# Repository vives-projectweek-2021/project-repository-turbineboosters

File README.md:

# TurbineBoosters
Welcome to our project repository!

## Choice of motor

To create our windturbine we had to make some choices. The first choice we had to make was wich motor to use as generator.
It soon became clear to us that we had to use a 3 phasse BLDC motor.
We looked around at our options and had 2 motors available, one that generates around 60V:

and another one that generates only around 6V, but has more power:

We decided to go for the motor that generates 60V because we lose 1,4V across the diodes of our 3 phase bridge rectifier and that leaves us with an efficiency of 96%, while the other motor would only offer us an efficiency of about 77%.

## Rectifier + first LoRa module

The power generated by our motor is fed to a 3 phase bridge rectifier.
On this board we measure the current and voltage via a shunt-resistor of 0,5Ω.
The LoRa module (RN2483A) receives this data and sends it peer-to-peer to another LoRa module:

## Lorawan receiver 

The data that we recieve over lorawan on the SODAQ Explorer microconroller is than formated to a byte array. Then the data is send over bluetooth and send to a raspberry pi.

First we wanted to send the data over bluetooth low energy that was on the controller. But the bleutooth HC05 chip doesn't take that much power and is easier to use. 

## Raspberry pi

The data that we receive over bluetooth is than but into an influxdb database. This data is than visualized with the use of grafana.

## Mechanical design

We mounted a bicycle wheel on the shaft of our motor, to which we attached 8 PVC-blades via 3D-printed coupling pieces.

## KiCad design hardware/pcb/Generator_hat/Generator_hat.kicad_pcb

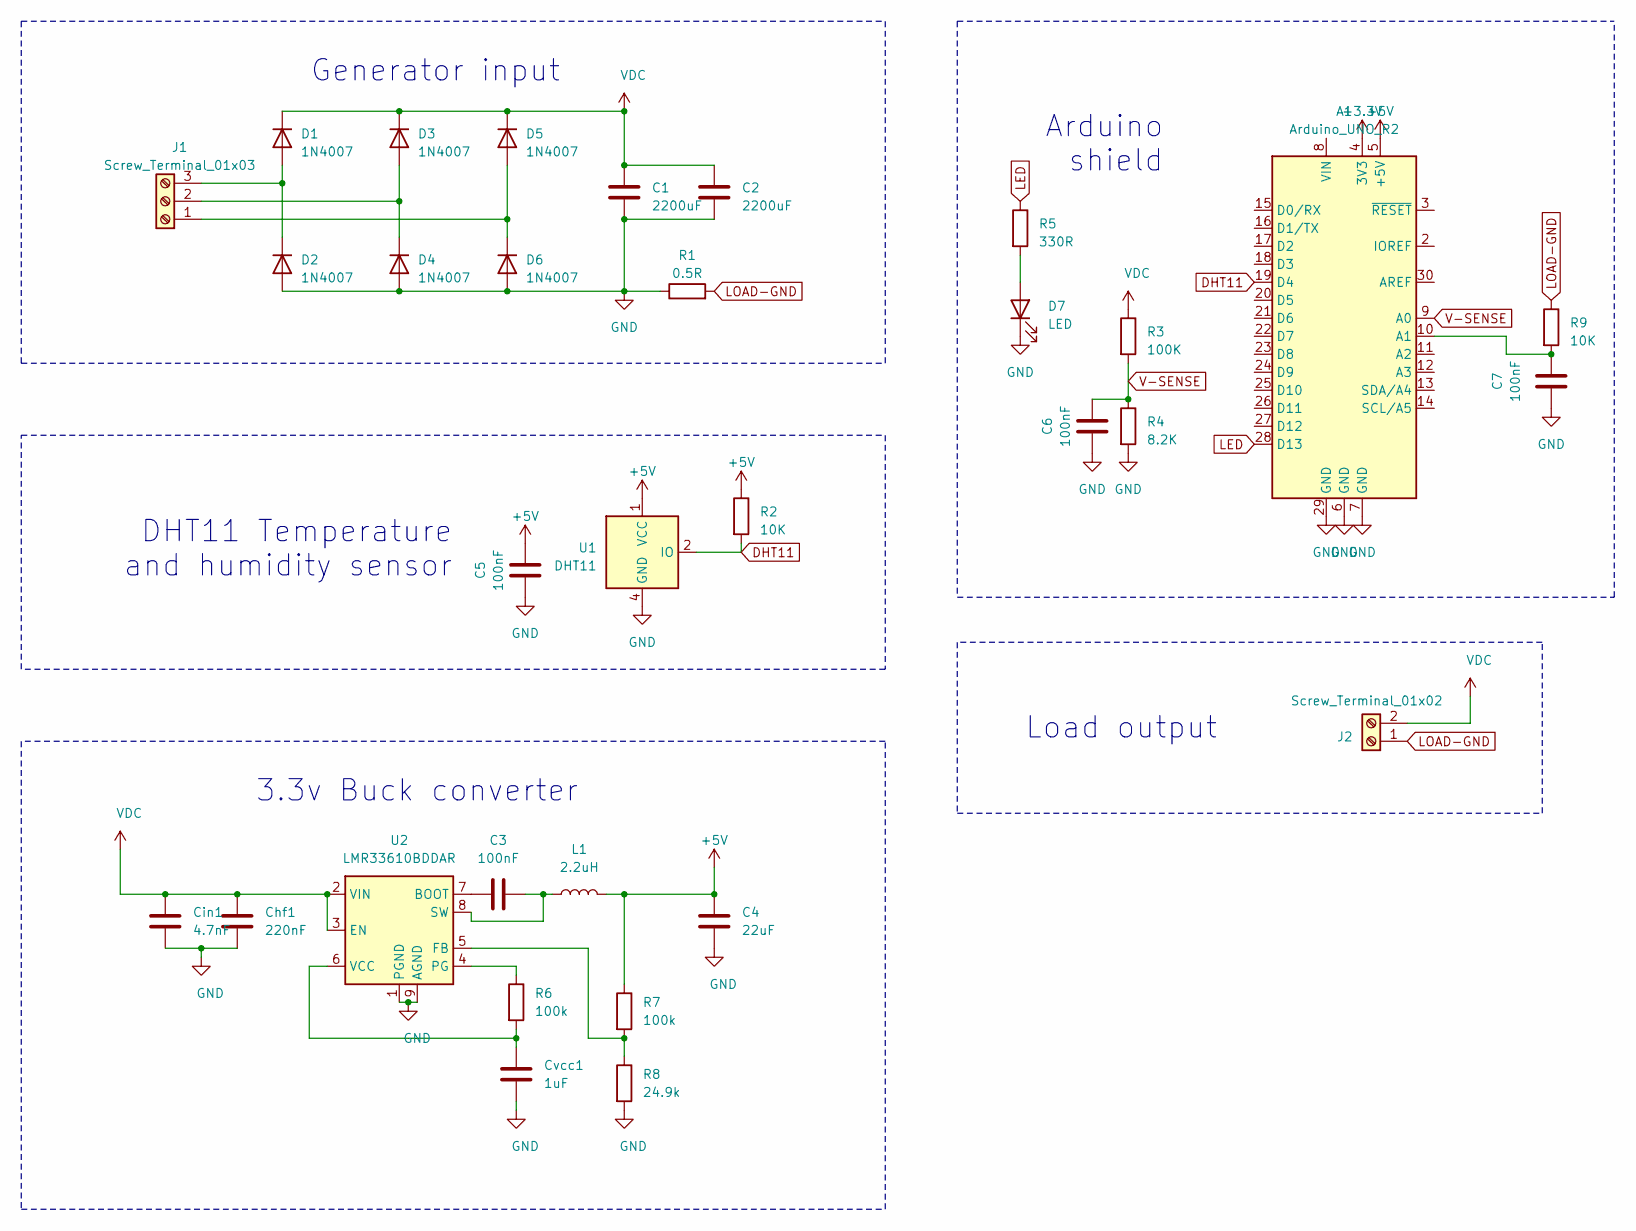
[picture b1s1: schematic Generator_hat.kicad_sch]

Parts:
A1: Arduino_UNO_R2
C1, C2: 2200uF; CP_Radial_D16.0mm_P7.50mm
C3, C5, C6, C7: 100nF; C_0805_2012Metric_Pad1.18x1.45mm_HandSolder
C4: 22uF; CP_Elec_8x6.9
Chf1: 220nF; C_0805_2012Metric_Pad1.18x1.45mm_HandSolder
Cin1: 4.7nF; C_0805_2012Metric_Pad1.18x1.45mm_HandSolder
Cvcc1: 1uF; C_0805_2012Metric_Pad1.18x1.45mm_HandSolder
D1, D2, D3, D4, D5, D6: 1N4007; D_SMA
D7: LED; LED_D3.0mm
J1: Screw_Terminal_01x03; TerminalBlock_bornier-3_P5.08mm
J2: Screw_Terminal_01x02; TerminalBlock_bornier-2_P5.08mm
L1: 2.2uH; L_Taiyo-Yuden_NR-50xx_HandSoldering
R1: 0.5R; R_Axial_DIN0309_L9.0mm_D3.2mm_P12.70mm_Horizontal
R2, R9: 10K; R_0805_2012Metric_Pad1.20x1.40mm_HandSolder
R3: 100K; R_0805_2012Metric_Pad1.20x1.40mm_HandSolder
R4: 8.2K; R_0805_2012Metric_Pad1.20x1.40mm_HandSolder
R5: 330R; R_0805_2012Metric_Pad1.20x1.40mm_HandSolder
R6, R7: 100k; R_0805_2012Metric_Pad1.20x1.40mm_HandSolder
R8: 24.9k; R_0805_2012Metric_Pad1.20x1.40mm_HandSolder
U1: DHT11; Aosong_DHT11_5.5x12.0_P2.54mm
U2: LMR33610BDDAR; Texas_HSOP-8-1EP_3.9x4.9mm_P1.27mm_ThermalVias

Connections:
+3V3: A1.4 (3V3)
+5V: A1.5 (+5V), C4.1, C5.1, L1.2, R2.1, R7.1, U1.1 (VCC)
DHT11: A1.19 (D4), R2.2, U1.2 (IO)
GND: A1.6 (GND), A1.7 (GND), A1.29 (GND), C1.2, C2.2, C4.2, C5.2, C6.2, C7.2, Chf1.2, Cin1.2, Cvcc1.2, D2.2 (A), D4.2 (A), D6.2 (A), D7.1 (K), R1.1, R4.2, R8.2, U1.4 (GND), U2.1 (PGND), U2.9 (AGND)
LED: A1.28 (D13), R5.1
LOAD-GND: J2.1, R1.2, R9.1
unnamed: A1.10 (A1), C7.1, R9.2
unnamed: C3.1, L1.1, U2.8 (SW)
unnamed: C3.2, U2.7 (BOOT)
unnamed: Cvcc1.1, R6.2, U2.6 (VCC)
unnamed: D1.2 (A), D2.1 (K), J1.3
unnamed: D3.2 (A), D4.1 (K), J1.2
unnamed: D5.2 (A), D6.1 (K), J1.1
unnamed: D7.2 (A), R5.2
unnamed: R6.1, U2.4 (PG)
unnamed: R7.2, R8.1, U2.5 (FB)
V-SENSE: A1.9 (A0), C6.1, R3.2, R4.1
VDC: C1.1, C2.1, Chf1.1, Cin1.1, D1.1 (K), D3.1 (K), D5.1 (K), J2.2, R3.1, U2.2 (VIN), U2.3 (EN)

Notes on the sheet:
DHT11 Temperature and humidity sensor
Generator input
3.3v Buck converter
Arduino shield
Load output

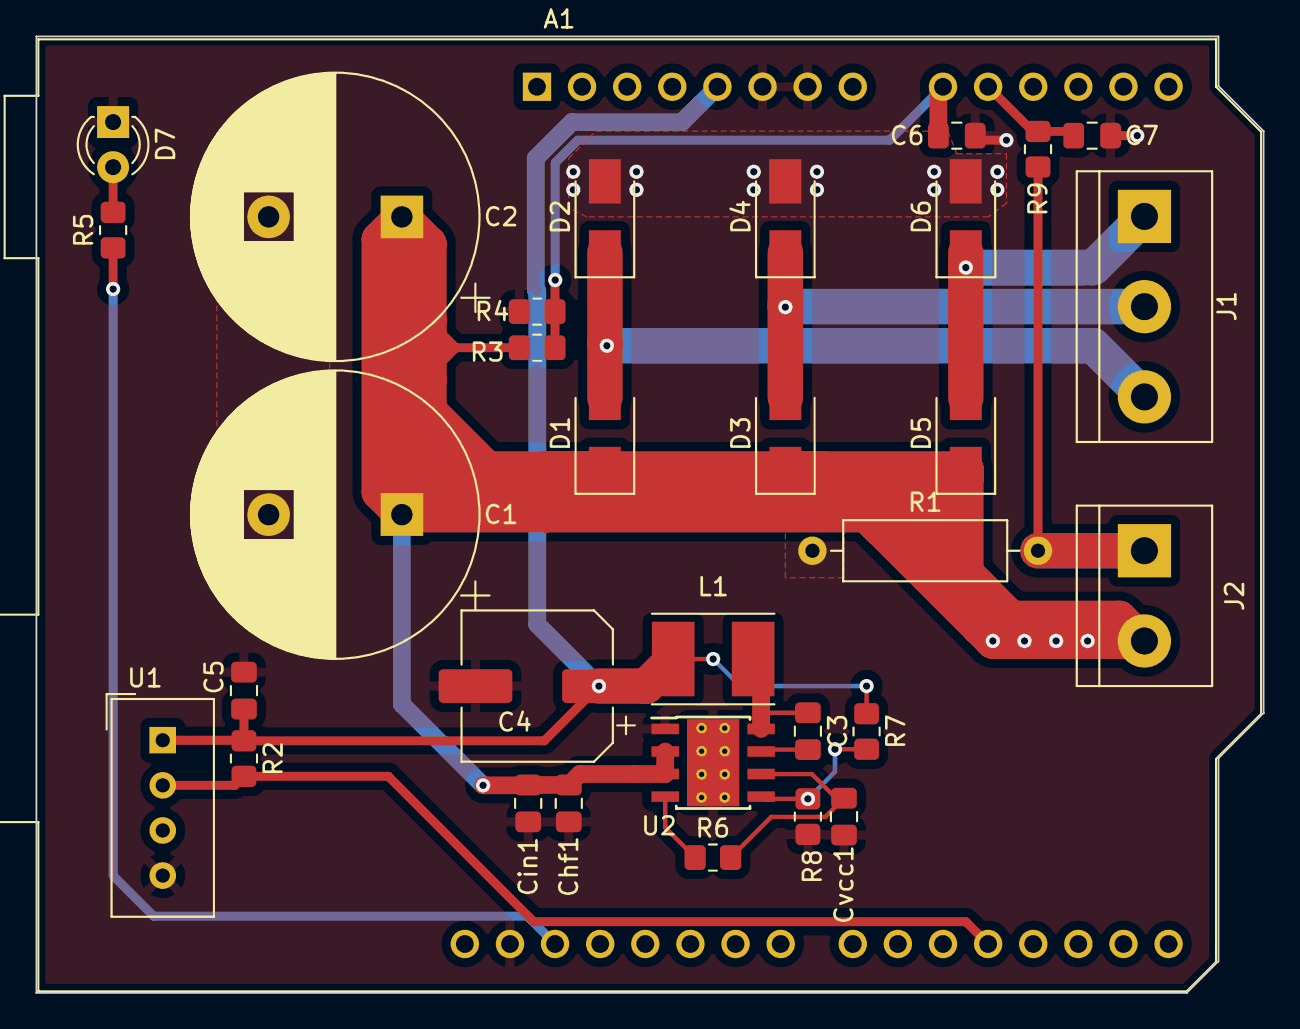
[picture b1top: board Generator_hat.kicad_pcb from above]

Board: 2 copper layers, 69.1 x 53.8 mm, 32 parts (0 on the bottom side), 17 nets.

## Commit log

2021-03-29 Added folder structure
2021-04-02 added kicad project with basic ac to dc convertion schematic
2021-04-02 added gitignore
2021-04-02 added voltage and current sensing to schematic
2021-04-05 Removed backup files
2021-04-05 Added gitignore for future kicad backups
2021-04-05 Added sensor-hat pcb
2021-04-05 Added DS_STORE to gitignore
2021-04-30 added presentation
2021-05-01 added Arduino software submodule
2021-05-07 added gif to powerpoint
2021-05-07 Added monitoring software
2021-05-07 Added docker-compose file
2021-05-07 Updating Readme
2021-05-08 added 3d printed parts and blender project
2021-05-08 added pcb and schematic
2021-05-10 updated ppt
2021-05-10 powerpoint
2021-05-10 updated arduino code
2021-05-15 Updating presentation
2021-05-18 update pcb
